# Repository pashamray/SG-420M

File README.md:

# SG-420M

Прошивка модифицирована для работы с экранами на контроллере [HD44780](https://ru.wikipedia.org/wiki/HD44780), размером 16x2, такими как WH1602.
Подключение экрана аналогично подключению в частотомере [FC-510](http://leoniv.diod.club/projects/measuring/fc-510/fc-510.html)

#### Общий вид генератора

#### Вид лицевой панели

#### Схема подключения экрана

#### Автор конструкций генератора и базовой прошивки

Ридико Леонид Иванович
* http://www.leoniv.diod.club
* http://leoniv.livejournal.com
* wubblick@yahoo.com

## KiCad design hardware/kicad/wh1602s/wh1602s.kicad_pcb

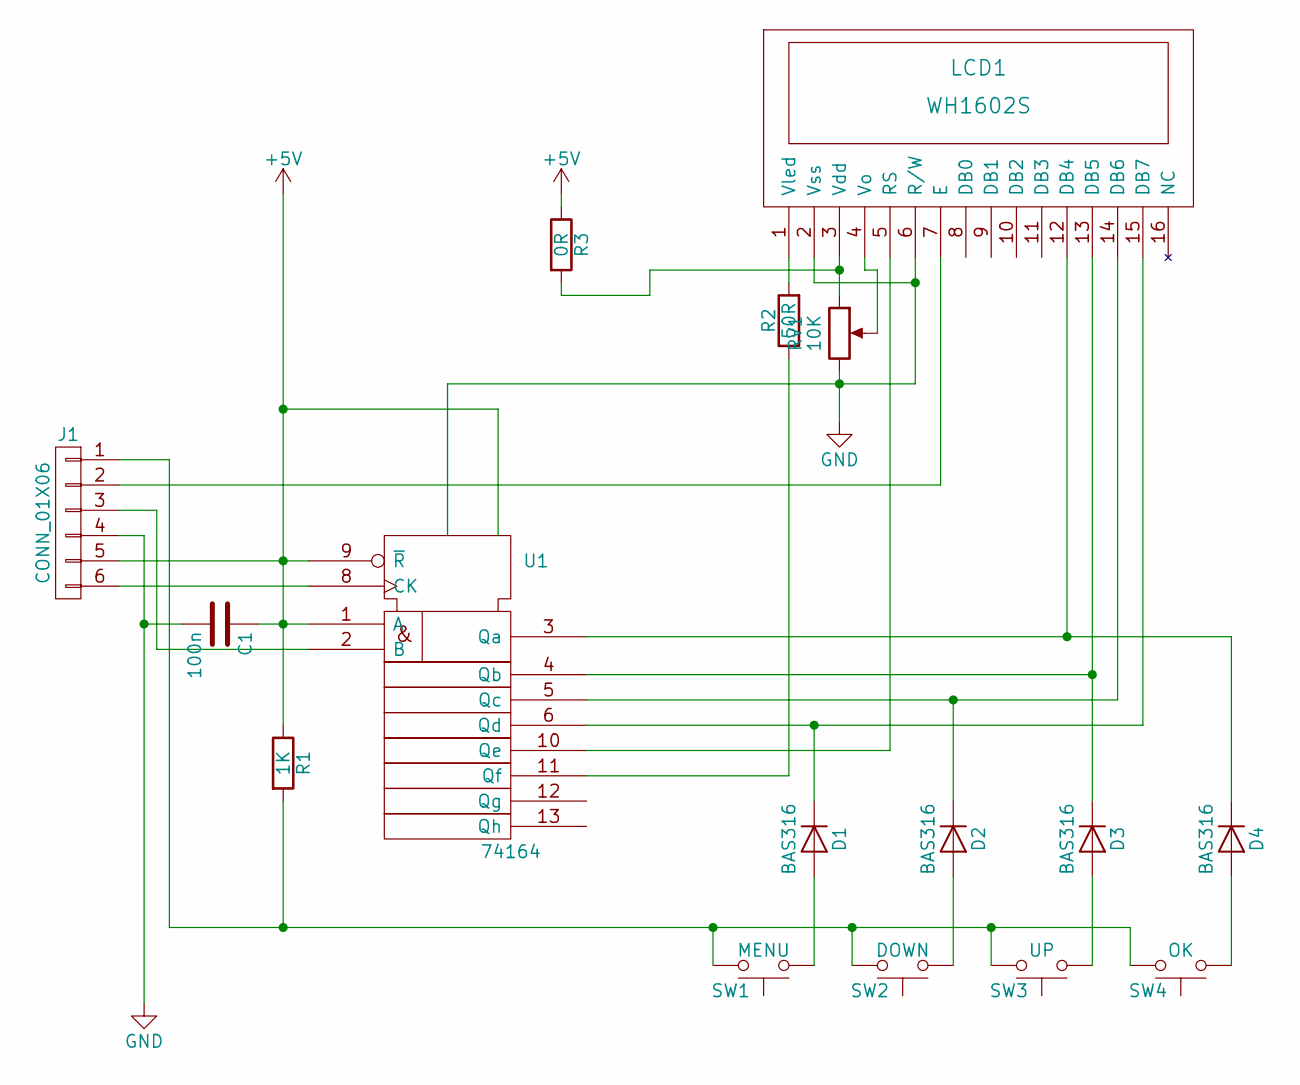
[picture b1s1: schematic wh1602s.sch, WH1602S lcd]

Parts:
C1: 100n; C_0805
D1, D2, D3, D4: BAS316; D_SOD-323
J1: CONN_01X06; Socket_Strip_Straight_1x06_Pitch2.54mm
LCD1: WH1602S
R1: 1K; R_0805
R2: 50R; R_0805
R3: 0R; R_0805
RV1: 10K; Potentiometer_Trimmer_Bourns_3296W
SW1: MENU; SW_PUSH-12mm
SW2: DOWN; SW_PUSH-12mm
SW3: UP; SW_PUSH-12mm
SW4: OK; SW_PUSH-12mm
U1: 74164; SOIC-14_N

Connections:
+5V: C1.1, J1.5, R1.1, R3.1, U1.1 (A), U1.9 (~R), U1.14 (Vdd)
GND: C1.2, J1.4, LCD1.2 (Vss), LCD1.6 (R/W), RV1.3, U1.7 (Vss)
unnamed: D1.1 (K), LCD1.15 (DB7), U1.6 (Qd)
unnamed: D1.2 (A), SW1.1
unnamed: D2.1 (K), LCD1.14 (DB6), U1.5 (Qc)
unnamed: D2.2 (A), SW2.1
unnamed: D3.1 (K), LCD1.13 (DB5), U1.4 (Qb)
unnamed: D3.2 (A), SW3.1
unnamed: D4.1 (K), LCD1.12 (DB4), U1.3 (Qa)
unnamed: D4.2 (A), SW4.1
unnamed: J1.1, R1.2, SW1.2, SW2.2, SW3.2, SW4.2
unnamed: J1.2, LCD1.7 (E)
unnamed: J1.3, U1.2 (B)
unnamed: J1.6, U1.8 (CK)
unnamed: LCD1.1 (Vled), R2.2
unnamed: LCD1.3 (Vdd), R3.2, RV1.1
unnamed: LCD1.4 (Vo), RV1.2
unnamed: LCD1.5 (RS), U1.10 (Qe)
unnamed: R2.1, U1.11 (Qf)

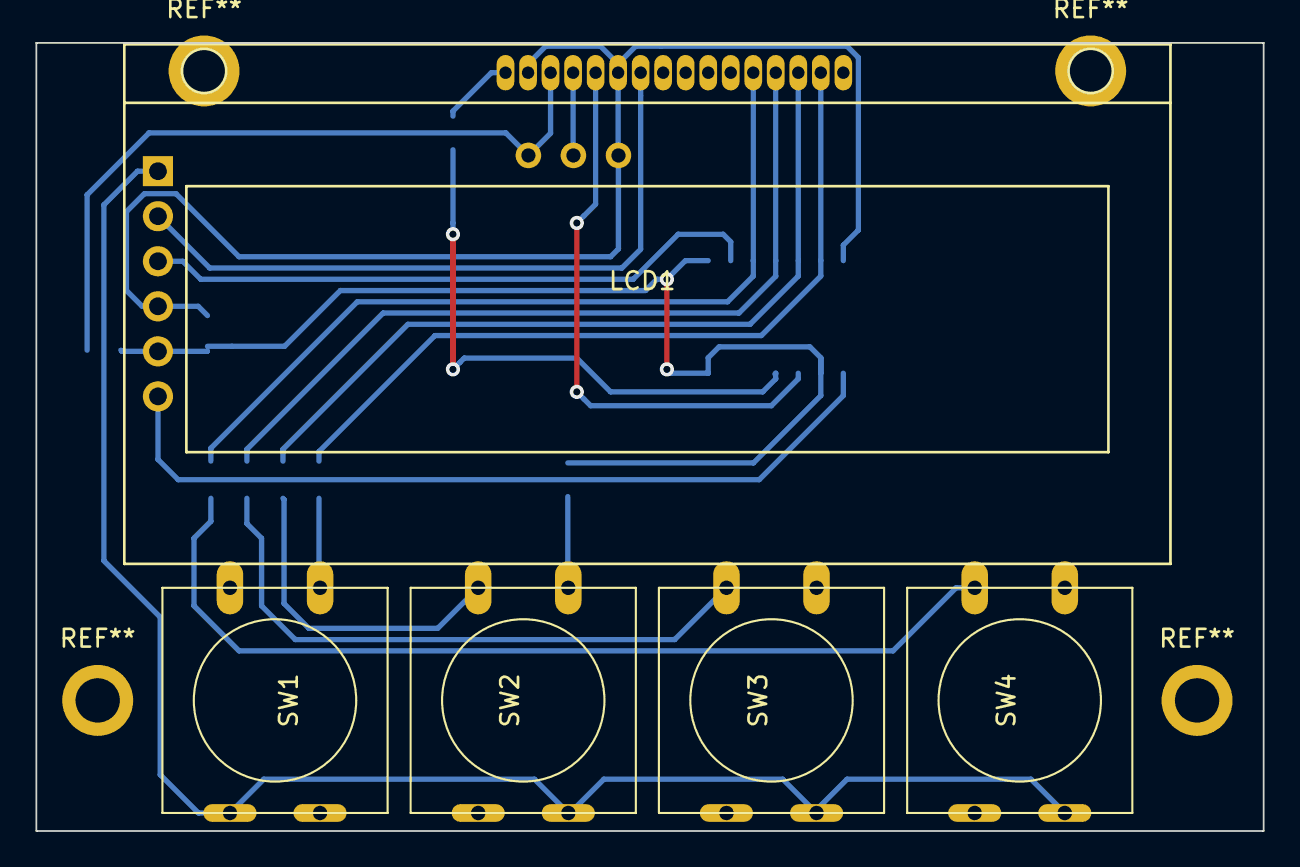
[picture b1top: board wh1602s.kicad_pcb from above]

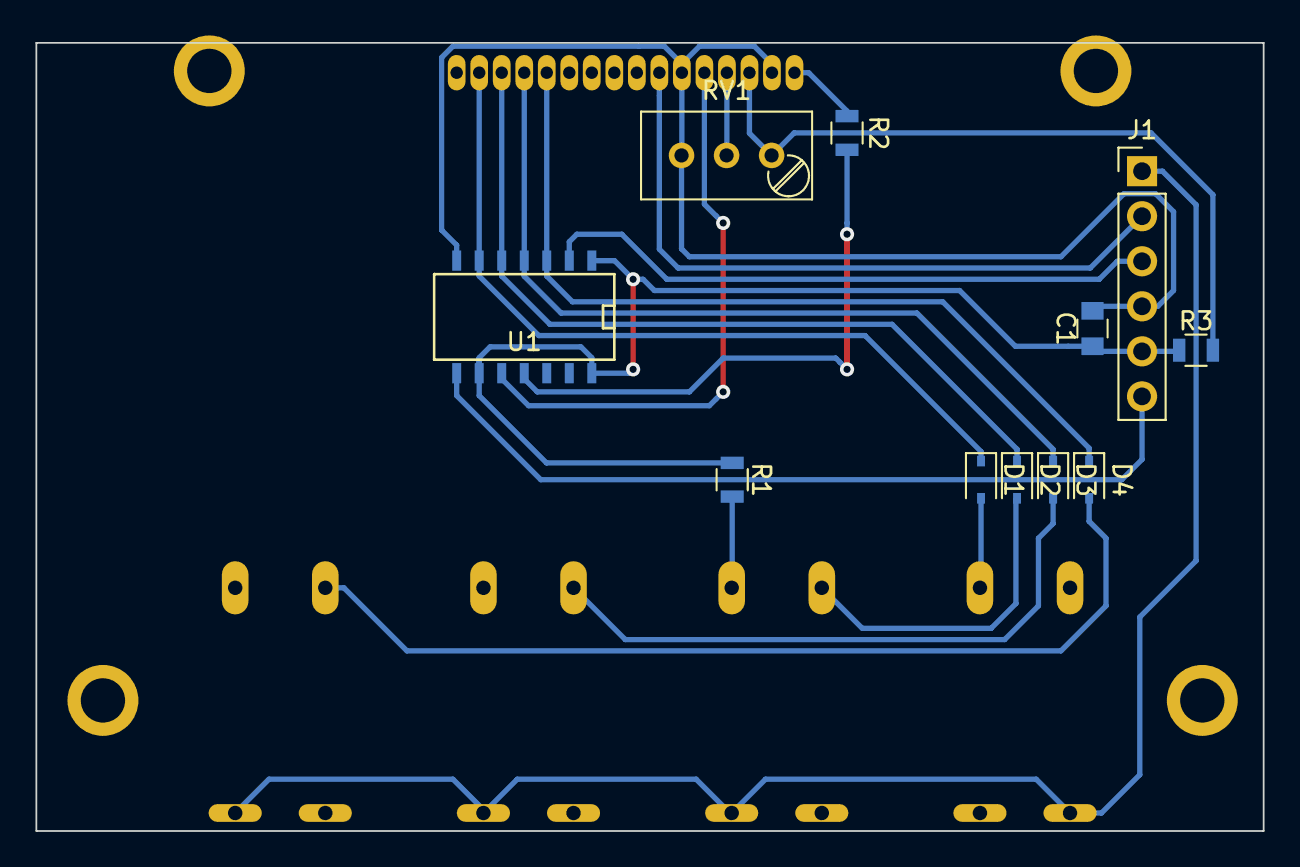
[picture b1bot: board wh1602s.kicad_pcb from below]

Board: 2 copper layers, 69.2 x 44.5 mm, 16 parts (11 on the bottom side), 19 nets.

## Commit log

2016-12-12 refactor
2016-12-14 add case doc
2017-01-02 add mech and pan
2017-01-10 add sources refactor
2017-01-10 add macros.mac edit build file
2017-01-10 update avrstudio project files
2017-01-11 add LCD_1602.asm comment output block code for simulate add proteus simulate file edit build script
2017-01-11 add wait.asm
2017-01-11 run testing init
2017-01-11 fix data out swap
2017-01-11 fix data out
2017-01-12 fix Init
2017-01-12 del proteus files fix data out
2017-01-13 add nop timing to init
2017-01-15 edit for proteus
2017-01-16 out first line
2017-01-17 refactor add strings
2017-01-17 fuck
2017-01-18 out 1 line Frequency, 2 line kHz
2017-01-18 add tmp to .gitignore
2017-01-18 edit address for 1 line
2017-01-18 other
2017-01-18 out zero digits
2017-01-19 return font table
2017-01-19 fix menu
2017-04-13 add gavrasm branch
2017-04-13 avra
2017-04-13 add flash.sh
2017-05-09 add point
2017-05-09 compile from avrstudio 7
2017-05-10 rename files
2017-05-10 move files
2017-05-10 rename macros.asm -> macros.inc
2017-05-11 add Hz and kHz
2017-05-16 del proteus files
2017-05-16 add face grafics for wh1602s
2017-05-16 add old png view add new png view
2017-05-16 add doc sch for wh160x add hardware sch wh1602x
2017-05-17 add new photo main view
2017-05-17 fix color for images
2017-05-21 fix image wh1602s
2017-06-06 add freecad wh1602s model files add kicad wh1602s pcb files
2024-08-09 Create LICENSE
